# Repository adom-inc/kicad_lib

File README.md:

# kicad_lib

> [!WARNING]
> This library is still in active development. All APIs and data structures are subject to change.

A Rust library for working with [KiCad](https://www.kicad.org/) files. This library handles the parsing and serialization of the KiCad file formats while also providing helpful functionality for generating and manipulating many of the internal structures used in the formats.

## Structure

-   [`kicad_sexpr`](/kicad_sexpr) - A crate for parsing the KiCad S-Expression format into a friendly tree representation. If you want to parse out the tree structure agnostic to the actual KiCad data format, then this is the crate to use.
-   [`kicad_format`](/kicad_format) - A crate for parsing the sexpr trees into a Rust interpretation of the structures used in the file formats. If you are only trying to manipulate the underlying data and not the S-Expression tree directly, then this is the crate to use.

## Usage

Since this library is not hosted on [crates.io](https://crates.io), to use it simply add the following to your `Cargo.toml` file:

```toml
kicad_sexpr = { git = "https://github.com/adom-inc/kicad_lib" }
```

or

```toml
kicad_format = { git = "https://github.com/adom-inc/kicad_lib" }
```

## Documentation

The documentation for this library is still work in progress, but you can bring up the documentation for the crate you are using with:

```console
$ cargo doc --package kicad_sexpr --open
```

or

```console
$ cargo doc --package kicad_format --open
```

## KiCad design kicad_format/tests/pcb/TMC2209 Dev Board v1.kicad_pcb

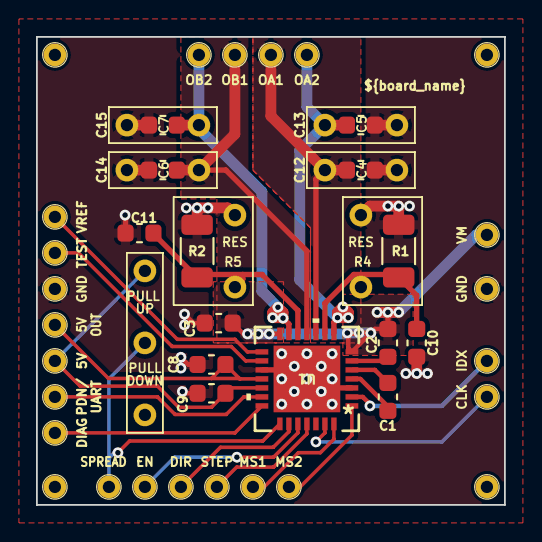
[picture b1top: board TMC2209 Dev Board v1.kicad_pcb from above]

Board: 4 copper layers, 26.0 x 26.0 mm, 46 parts (0 on the bottom side), 25 nets.

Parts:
C1: 22nF; C_0603_1608Metric
C2, C3, C9, C10, C11: 100nF; C_0603_1608Metric
C4, C5, C6, C7: 1nF; ADOM_CAPACITOR_CHIP_6x2
C8: 2.2uF; C_0603_1608Metric
C12, C13, C14, C15: 1nF; C_0603_1608Metric
R1, R2: 0.15r/1%; R_1206_3216Metric
R4, R5: 0.15r/1%; ADOM_Resistor_1206
RSelect1: Adom_R_3Way_Pullup_or_Pulldown; ADOM_RESISTOR_CHIP_6x2_3Way_Selector
U1: QFN28_5X5_TRI
X1, X2, X3, X4: ADOM_MECHANICAL_PIN; ADOM_MEDIUM_PIN
X5, X6, X7, X8, X9, X10, X11, X12, X13, X14, X15, X16, X17, X18, X19, X20, X21, X22, X23, X24, X25: ADOM_MEDIUM_SPRING_CONTACT

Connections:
5V: C9.2, RSelect1.1, U1.19 (VCC_IO), X22.1 (SIG_PIN)
5VOUT: C8.2, U1.18 (5VOUT), X24.1 (SIG_PIN)
CLK: U1.27 (CLK), X5.1 (SIG_PIN)
DIAG: U1.21 (DIAG), X19.1 (SIG_PIN)
DIR1: U1.23 (DIR), X11.1 (SIG_PIN)
EN1: U1.24 (ENN), X13.1 (SIG_PIN)
GND: C3.1, C4.2, C5.2, C6.2, C7.2, C8.1, C9.1, C10.1, C11.1, C12.2, C13.2, C14.2, C15.2, R1.2, R2.2, R4.1, R5.2, RSelect1.3, U1.3 (GND), U1.17 (GND), U1.PAD (GND), X21.1 (SIG_PIN), X25.1 (SIG_PIN)
INDEX: U1.2 (INDEX), X18.1 (SIG_PIN)
MS1: U1.28 (MS1), X10.1 (SIG_PIN)
MS2: U1.1 (MS2), X9.1 (SIG_PIN)
unnamed: C10.2, R1.1, R4.2, U1.9 (BRA)
unnamed: C11.2, R2.1, R5.1, U1.12 (BRB)
unnamed: C1.1, U1.5 (CPI)
unnamed: C1.2, U1.4 (CPO)
unnamed: U1.16 (TEST), X23.1 (SIG_PIN)
unnamed: C2.1, U1.6 (VCP)
OA1: C4.1, C12.1, U1.10 (OA1), X14.1 (SIG_PIN)
OA2: C5.1, C13.1, U1.8 (OA2), X15.1 (SIG_PIN)
OB1: C6.1, C14.1, U1.11 (OB1), X16.1 (SIG_PIN)
OB2: C7.1, C15.1, U1.13 (OB2), X17.1 (SIG_PIN)
PDN/UART: U1.20 (PDN_UART), X7.1 (SIG_PIN)
SPREAD: RSelect1.2, U1.22 (SPREAD), X8.1 (SIG_PIN)
STEP1: U1.25 (STEP), X12.1 (SIG_PIN)
VM: C2.2, C3.2, U1.7 (VS), U1.14 (VS), X20.1 (SIG_PIN)
VREF: U1.15 (VREF), X6.1 (SIG_PIN)

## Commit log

2024-05-07 release for open source
2024-05-29 feat: add serde feature
2024-05-29 fix: add serde content where needed
2024-05-29 fix: remove unnecessary serde tags
2024-05-29 style: fix formatting
2024-05-31 start of kicad 8 support
2024-06-03 initial tests passing
2024-06-10 feat: impl FromSexpr for PcbDimension
2024-06-10 feat: impl ToSexpr for PcbDimension
2024-06-10 feat: add pcb generators
2024-08-04 Add netlist file support
2025-07-04 chore: update Cargo.toml to support wasm
2025-07-04 feat: add dnp field to footprint attribute
2025-07-04 fix: update group parsing
2025-07-04 feat: add support for base64 decoding
2025-07-05 feat: new lexer implementation
2025-09-20 Fully passing tests
2025-09-23 feat: add initial support for kicad 9
2025-09-23 fix: more updates for kicad 9
